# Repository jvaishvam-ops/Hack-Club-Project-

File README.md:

# Hack-Club-Projects-

## Project Overview

This project is a custom PCB design for a compact input/control board built around a microcontroller footprint and four push-button switch positions. The design includes the complete board layout, fabrication outputs, and a compact mechanical control interface intended for study-session productivity use.

## How The Timer Works

The Lock-In Clock is a productivity tracker designed to help me stay focused during study sessions. At its core, it acts as a Pomodoro timer. When powered on, the Raspberry Pi Pico W runs a MicroPython script that tracks countdown time, updates the display, and reads button inputs. The timer is centered around a 25-minute focus block and can be adjusted in 5-minute increments using the physical buttons on the custom PCB.

## What The 4 Buttons Do

I designed the custom PCB to hold 4 tactile Cherry MX Brown mechanical switches to control the timer without needing a mouse or keyboard.

- **Button 1 (Start/Pause):** Toggles the timer on or off. When pressed, the screen updates to say "LOCK IN" and the countdown begins. Pressing it again pauses the timer.
- **Button 2 (Reset):** Stops the timer immediately and resets the clock back to the default 25 minutes.
- **Button 3 (Add Time):** Adds 5 minutes (300 seconds) to the current timer block if I feel like I need a longer study session.
- **Button 4 (Subtract Time):** Subtracts 5 minutes from the current timer block in case I want a shorter sprint.

## How I Used AI in the PCB Layout

I used AI (specifically a large language model) as a troubleshooting and learning assistant while designing the PCB in KiCad. Because this was my first time designing a custom board, I used AI to help reason through layout constraints, component placement, signal routing, and the overall mechanical fit of the Raspberry Pi Pico W and button array.

## Included Design Files

- [BOM.md](BOM.md) — bill of materials
- [JOURNAL.md](JOURNAL.md) — build and design notes
- [README.md](README.md) — project documentation

## KiCad Project Files

The main KiCad source files for the PCB project are kept in the repository root so they can be opened directly in KiCad:

- [week 1 lock in module .kicad_pro](week%201%20lock%20in%20module%20.kicad_pro)
- [week 1 lock in module .kicad_sch](week%201%20lock%20in%20module%20.kicad_sch)
- [week 1 lock in module .kicad_pcb](week%201%20lock%20in%20module%20.kicad_pcb)
- [week 1 lock in module .kicad_prl](week%201%20lock%20in%20module%20.kicad_prl)

## Schematic and Fabrication Files

The repository contains the complete set of PCB fabrication and schematic output files used for the board design:

- [schematic-B_Cu.gbl](schematic-B_Cu.gbl)
- [schematic-B_Cu.gbr](schematic-B_Cu.gbr)
- [schematic-B_Mask.gbr](schematic-B_Mask.gbr)
- [schematic-B_Mask.gbs](schematic-B_Mask.gbs)
- [schematic-B_Paste.gbp](schematic-B_Paste.gbp)
- [schematic-B_Silkscreen.gbo](schematic-B_Silkscreen.gbo)
- [schematic-Edge_Cuts.gbr](schematic-Edge_Cuts.gbr)
- [schematic-Edge_Cuts.gm1](schematic-Edge_Cuts.gm1)
- [schematic-F_Cu.gbr](schematic-F_Cu.gbr)
- [schematic-F_Cu.gtl](schematic-F_Cu.gtl)
- [schematic-F_Mask.gts](schematic-F_Mask.gts)
- [schematic-F_Paste.gbr](schematic-F_Paste.gbr)
- [schematic-F_Paste.gtp](schematic-F_Paste.gtp)
- [schematic-F_Silkscreen.gbr](schematic-F_Silkscreen.gbr)
- [schematic-NPTH.drl](schematic-NPTH.drl)
- [schematic-PTH.drl](schematic-PTH.drl)
- [schematic-job.gbrjob](schematic-job.gbrjob)

## Project Gallery

The broken layout image links were replaced with the images uploaded above. These are the project images currently referenced in the gallery:

**1. Custom PCB Schematic:**

**2. Manufactured PCB (Delivered):**

## Notes

The repository is designed to document the PCB development process and provide the core fabrication-ready outputs for the project.

## Bill of Materials

| Part Name | Quantity | Unit Price | Buying Link |
| :--- | :--- | :--- | :--- |
| Raspberry Pi Pico W | 1 | 649.00 | [Robu.in](https://robu.in/) |
| 0.96 inch OLED with ssd1306 128x64 I2C | 1 | 169.00 | [Robu.in](https://robu.in/) |
| Mechanical Switch Brown Silent Click | 4 | 14.00 | [Sunrom.com](https://www.sunrom.com/) |
| Black DSA Keycap for MX Compatible | 4 | 19.00 | [Sunrom.com](https://www.sunrom.com/) |
| 1x40 Pin 2.54mm Female Strip | 2 | 98.00 | [Robu.in](https://robu.in/) |
| 1x40 Pin 2.54mm Male Header Strip | 2 | 9.00 | [Robu.in](https://robu.in/) |
| Custom PCB (55x79mm 2-layer) | 5 | N/A | [PCBPower.com](https://www.pcbpower.com/) |

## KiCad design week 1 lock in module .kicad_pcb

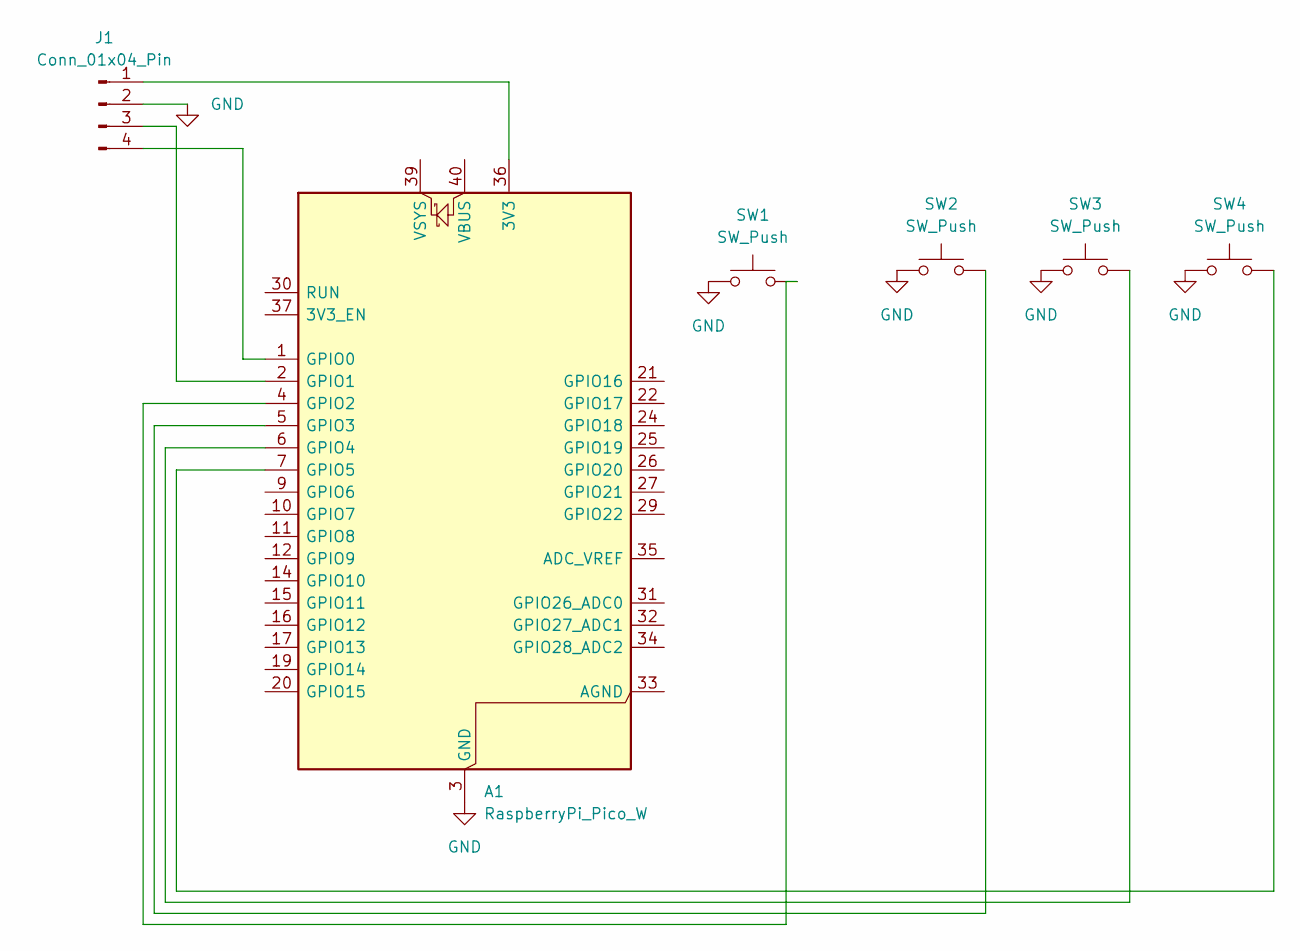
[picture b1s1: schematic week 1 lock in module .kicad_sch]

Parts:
A1: RaspberryPi_Pico_W; RaspberryPi_Pico_Common_THT
J1: Conn_01x04_Pin; PinHeader_1x04_P2.54mm_Vertical
SW1, SW2, SW3, SW4: SW_Push; SW_Cherry_MX_1.00u_PCB

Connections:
GND: A1.3 (GND), A1.8 (GND), A1.13 (GND), A1.18 (GND), A1.23 (GND), A1.28 (GND), A1.38 (GND), J1.2, SW1.1, SW2.1, SW3.1, SW4.1
unnamed: A1.36 (3V3), J1.1
unnamed: A1.1 (GPIO0), J1.4
unnamed: A1.2 (GPIO1), J1.3
unnamed: A1.4 (GPIO2), SW1.2
unnamed: A1.5 (GPIO3), SW2.2
unnamed: A1.6 (GPIO4), SW3.2
unnamed: A1.7 (GPIO5), SW4.2

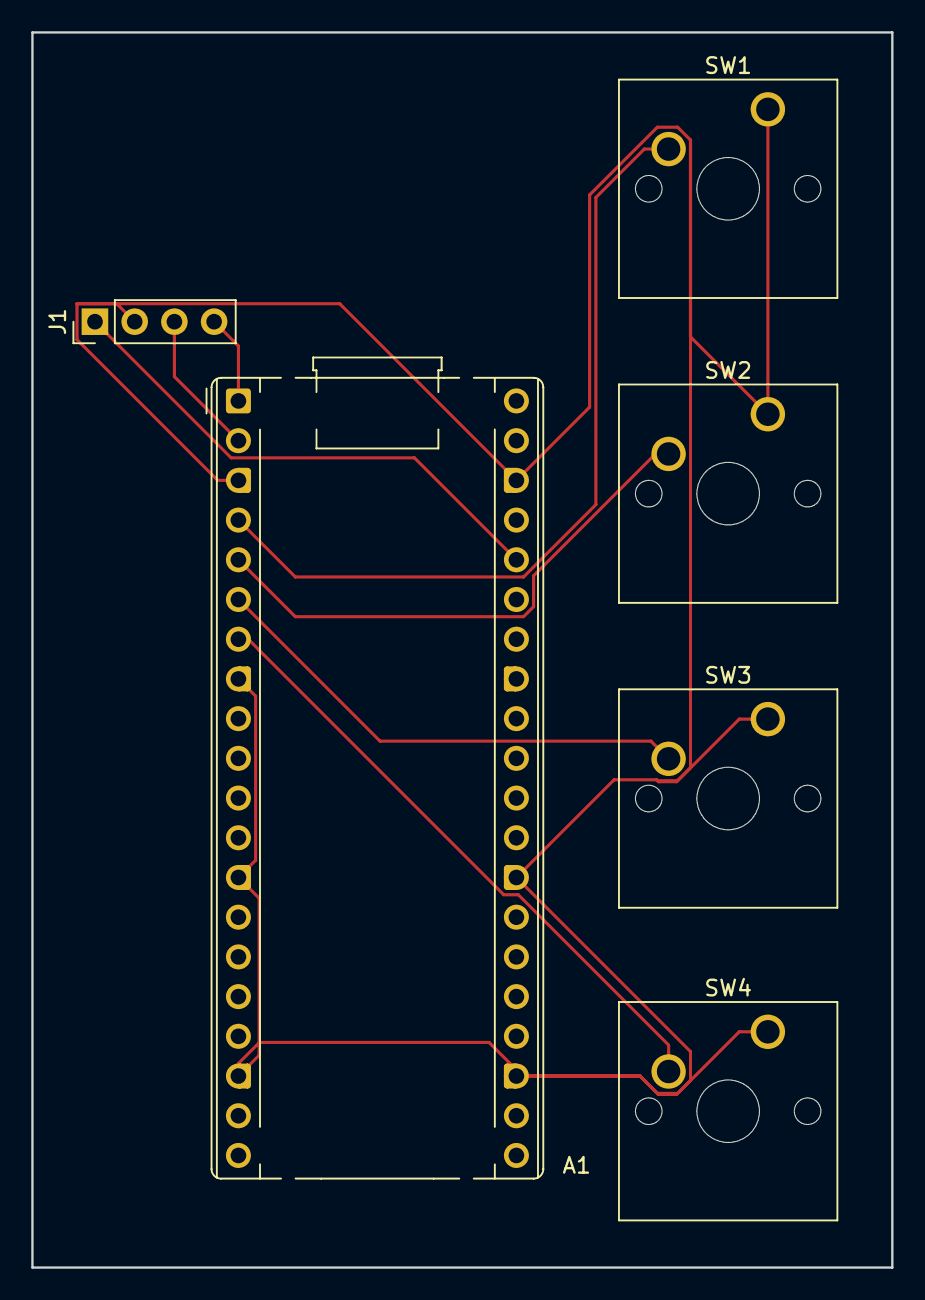
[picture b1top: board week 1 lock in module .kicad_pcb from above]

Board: 2 copper layers, 55.0 x 79.0 mm, 6 parts (0 on the bottom side), 8 nets.

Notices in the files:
week 1 lock in module .kicad_sch:
creativecommons.org/licenses/by/4.0
Licence CC by 4.0
